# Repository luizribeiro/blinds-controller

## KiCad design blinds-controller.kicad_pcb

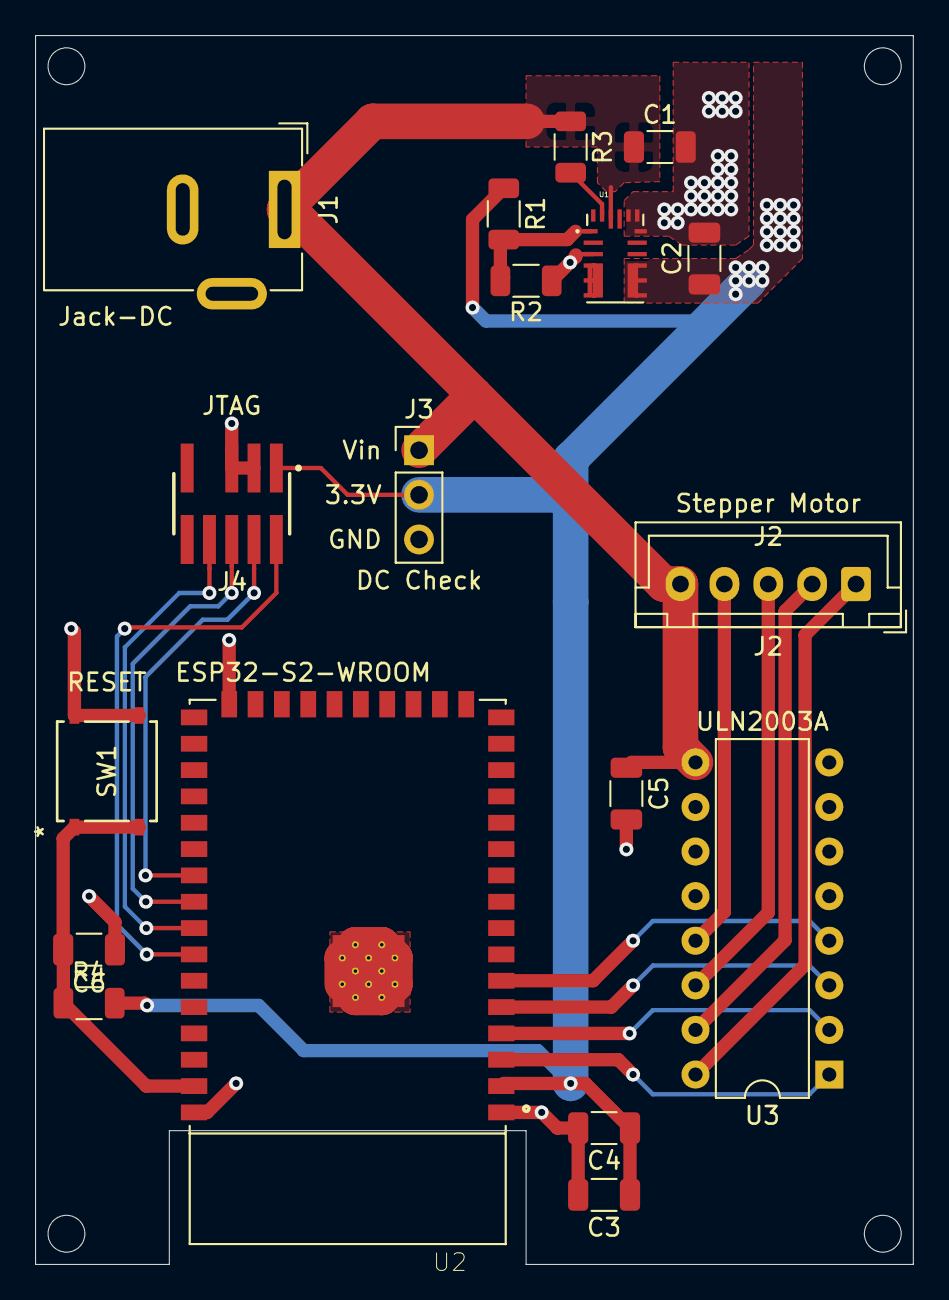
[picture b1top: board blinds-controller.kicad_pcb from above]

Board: 2 copper layers, 50.0 x 70.0 mm, 18 parts (0 on the bottom side), 19 nets.

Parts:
C1: 10uf; C_1206_3216Metric
C2, C3: 22uF; C_1206_3216Metric
C4: 0.1uF; C_1206_3216Metric
C5: 10uF; C_1206_3216Metric
C6: 1uf; C_1206_3216Metric
J1: Jack-DC; BarrelJack_Wuerth_6941xx301002
J2: Stepper Motor; JST_XH_B5B-XH-A_1x05_P2.50mm_Vertical
J3: DC Check; PinHeader_1x03_P2.54mm_Vertical
J4: JTAG; SAMTEC_FTSH-105-01-L-DV-007-K-P-TR
R1: 75k; R_1206_3216Metric
R2: 24k; R_1206_3216Metric
R3: 100k; R_1206_3216Metric
R4: 10k; R_1206_3216Metric
SW1: RESET; PTS526 SM15 SMTR2 LFS
U1: MPM3610AGQV-P; CONV_MPM3620AGQV-P
U2: ESP32-S2-WROOM; XCVR_ESP32-S2-WROOM
U3: ULN2003A; DIP-16_W7.62mm

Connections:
+3V3: C2.1, C3.1, C4.1, J3.2, J4.01, R1.1, R4.1, U1.7, U1.8, U1.9, U1.20, U2.2
+12V: C1.1, C5.1, J1.1, J2.5, J3.1, R3.1, U1.16, U3.9
GND: C1.2, C2.2, C3.2, C4.2, C5.2, C6.2, J1.2, J3.3, J4.03, J4.05, R2.2, SW1.3, SW1.4, U1.3, U1.12, U1.13, U1.14, U2.1, U2.26, U2.42, U2.43.1, U2.43.2, U2.43.3, U2.43.4, U2.43.5, U2.43.6, U2.43.7, U2.43.8, U2.43.9, U2.43.10, U2.43.11, U2.43.12, U2.43.13, U2.43.14, U2.43.15, U2.43.16, U2.43.17, U2.43.18, U2.43.19, U2.43.20, U2.43.21, U3.8
JTAG.TCK: J4.04, U2.33
JTAG.TDI: J4.08, U2.35
JTAG.TDO: J4.06, U2.34
JTAG.TMS: J4.02, U2.36
unnamed: J2.1, U3.16
unnamed: J2.2, U3.15
unnamed: J2.3, U3.14
unnamed: J2.4, U3.13
unnamed: R1.2, R2.1, U1.1
unnamed: R3.2, U1.17
unnamed: U1.4, U1.5, U1.6, U1.19
RESET: C6.1, R4.2, SW1.1, SW1.2, U2.41
Stepper.A: U2.3, U3.1
Stepper.B: U2.4, U3.2
Stepper.C: U2.5, U3.3
Stepper.D: U2.6, U3.4

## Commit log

2021-03-07 Added MPM3610AGQV-P as a buck converter
2021-03-07 Imported ESP32-S2-WROOM lib and datasheet
2021-03-07 Added ESP32-S2-WROOM library to project
2021-03-07 First routed version of PCB
2021-03-07 Added headers for testing voltage
2021-03-07 Added traces between GND pins on ESP32 bottom
2021-03-08 Added JTAG connector
2021-03-08 Added labels to DC check header
2021-03-08 Lots of small tweaks, almost there
    Just missing decoupling capacitors and a final review
2021-03-08 Small tweaks
2021-03-15 Added switch symbol to library
2021-03-15 Connected JTAG GND
2021-03-15 Added decoupling capacitors to ESP32
2021-03-15 Added decoupling capacitors to ULN2003A
2021-03-15 Added RESET switch and made some adjustments
2021-03-15 Opened up room for screw holes
2021-03-15 Increased trace width for 3v3 line near voltage regulator
2021-03-15 Added PCB holes
2021-04-11 Setup git filters for KiCad project and schematic
2023-12-15 Add renovate.json
